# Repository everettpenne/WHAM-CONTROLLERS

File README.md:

# WHAM controllers

Firmware, hardware files and host software for the WHAM controller board (STM32G474QET6) and the two
products that run on it.

```
firmware/
  xrex/      WHAM-XREX-PFMG474    Transrex magnet-supply PFM PID controller
  hbridge/   WHAM-HBRIDGE-PFMG474 3-phase H-bridge (Limiter PWM / HVPS PFM)
hardware/    board files, pin map, hardware notes (see hardware/README.md)
host/        host-side software that talks to the boards: the per-controller service (see docs/)
docs/        design documents that span products (identity, host service, repo layout)
```

Each firmware directory is a complete, self-contained project (its own AGENTS.md, build, tests, docs) and keeps its own
history, imported from the former standalone repositories. Code that both products share is still copied byte-for-byte
and guarded by `firmware/<product>/python/check_shared.py`; see each project's `docs/saved_profiles_shared.md`.

## History

This repository replaces the standalone `WHAM-XREX-PFMG474` and `WHAM-HBRIDGE-PFMG474` repositories (imported on 2026-10-07 with their
full histories; the old repositories stop at that point and are no longer updated). All the projects are maintained here from now on:
firmware for both products, the hardware files, the host software and the design documents. `docs/device_identity_and_host_service.md`
is the plan for board identity and the host service.

## License

The software is licensed under the GNU Affero General Public License v3.0 only (`AGPL-3.0-only`): see [`LICENSE`](LICENSE).
What that covers, what keeps its own license (the ST and Arm vendor code), and what is not licensed yet (documents and
hardware designs) is spelled out in [`LICENSING.md`](LICENSING.md).

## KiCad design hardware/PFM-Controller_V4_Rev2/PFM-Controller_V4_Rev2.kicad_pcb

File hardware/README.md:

# Hardware

KiCad projects for the WHAM controller board and its predecessors, with their fabrication outputs.

| Folder | What |
|---|---|
| `PFM-Controller_V4/` | the current controller board (STM32G474QET6, pin map in `firmware/*/docs/pin_mapping_v4.csv`) |
| `PFM-Controller_V4_Rev2/` | a second revision of the V4 board (KiCad project) |
| `HVPS_Controller_V3/` | the previous board (V3) |

Not tracked on purpose (see `.gitignore`): KiCad backups, autosaves and caches, the fabrication toolkit's `production/backups/`, and
large third-party document archives (`hardware/*.zip`; GitHub refuses files over 100 MB). `PFM-Controller_V4/PFMV4_Prelim_Files-main/`
(a downloaded copy of earlier project files and documents) is left untracked until someone decides it belongs here.

The pin map still lives with each firmware project (the firmware, the SOP and the command reference point at it). Moving it here, with
product columns beside it and a changelog of board revisions, is the natural next step.

**License:** the hardware designs are not licensed yet (all rights reserved); the AGPL in the repository root covers the software only.
See `LICENSING.md`.

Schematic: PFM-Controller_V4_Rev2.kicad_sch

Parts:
C1, C2: 100u
C31, C61, C62, C63, C64, C65, C66, C67, C68, C69, C70, C71, C72, C73, C74, C75, C76, C77, C78, C79, C80, C81, C82, C83, C84, C85, C86, C87, C88, C89, C90, C91, C92, C93, C94, C95, C96, C97, C98, C99, C100, C101, C102, C103, C104, C105, C112, C116, C117, C118, C124, C125, C126, C127, C129, C130: 100n; C_0805_2012Metric_Pad1.18x1.45mm_HandSolder
C33, C36, C37, C38, C39, C40, C41, C42, C43: 100n; C_0603_1608Metric_Pad1.08x0.95mm_HandSolder
C44: 10u; C_0603_1608Metric_Pad1.08x0.95mm_HandSolder
C45, C47: 1u; C_0603_1608Metric_Pad1.08x0.95mm_HandSolder
C46: 10n; C_0603_1608Metric_Pad1.08x0.95mm_HandSolder
C48, C113, C119, C121, C123: 100n; R_0603_1608Metric_Pad0.98x0.95mm_HandSolder
C49, C50: 16pF; C_0805_2012Metric_Pad1.18x1.45mm_HandSolder
C51, C52, C53, C54, C55, C56, C58, C138, C139, C140, C141, C142, C143, C144, C145, C146: C; C_1206_3216Metric_Pad1.33x1.80mm_HandSolder; not fitted
C59: 10n; C_1206_3216Metric_Pad1.33x1.80mm_HandSolder
C60: 1u; C_1206_3216Metric_Pad1.33x1.80mm_HandSolder
C106, C107, C108, C109, C110, C111, C114, C120, C131, C132, C133, C134, C135, C136, C137, C147, C148, C149, C150, C151, C152, C153: 100n; C_1206_3216Metric_Pad1.33x1.80mm_HandSolder
D1, D2, D3, D4, D6, D7, D8, D9: BAV99S; SOT-363_SC-70-6
D5, D10, D11, D12, D13, D14, D15, D16: LED; LED_0805_2012Metric
D17, D18, D19, D20: CMKD4448; SOT-363_SC-70-6
FB1: 120R @ 100MHz; Ferrite_1206_3216Metric_Pad1.42x1.75mm_BigPads
FB2, FB3, FB4, FB5, FB6, FB7, FB8, FB9, FB10, FB11, FB12, FB13, FB14, FB15, FB16, FB17, FB18, FB19, FB20, FB21, FB22, FB23, FB24, FB25, FB26, FB27: 110R @ 30MHz; Ferrite_1206_3216Metric_Pad1.42x1.75mm_BigPads
H1, H2, H3, H4, H5, H6, H7, H8, H9, H10, H11, H12, H13, H14, H15, H16, H17, H18: MountingHole; MountingHole_2mm
IC1, IC2, IC3, IC4, IC5, IC6, IC7, IC8, IC9, IC10, IC11, IC12, IC13, IC14, IC15, IC16, IC17, IC18, IC19, IC20, IC21: IX4340NTR; SOIC-8_3.9x4.9mm_P1.27mm; Mouser Part Number 747-IX4340NTR
J1, J2, J3, J4, J5, J6, J7, J8: BNC; BNC_TEConnectivity_1478204_Vertical; not fitted
J9: Conn_01x04_Pin; Molex_KK-254_AE-6410-04A_1x04_P2.54mm_Vertical
J10, J11, J12, J20: Molex 01x03; Molex_KK-254_AE-6410-03A_1x03_P2.54mm_Vertical
J13: Conn_01x04_Pin; Molex_KK-396_5273-04A_1x04_P3.96mm_Vertical
J16: Conn_01x06_Pin; Molex_KK-254_AE-6410-06A_1x06_P2.54mm_Vertical
J21: Conn_01x30_Pin; PinHeader_2x15_P2.54mm_Vertical
J22: Conn_01x16_Pin; PinHeader_2x08_P2.54mm_Vertical
R1, R2, R3, R4, R5, R6, R9, R10, R11, R12, R13, R14, R30, R31, R41, R63, R65, R92, R209, R228: 5K; R_0805_2012Metric_Pad1.20x1.40mm_HandSolder
R7, R27, R28, R29, R32, R33, R46, R47, R71, R74, R76, R104, R106, R108, R110, R112, R114, R117, R119: 5K; R_1206_3216Metric_Pad1.30x1.75mm_HandSolder
R15, R16, R17, R18, R19, R20, R21, R22, R23, R24, R25, R26, R51, R52, R53, R54, R55, R56, R57, R58, R59, R60, R61, R62, R77, R78, R95, R96, R97, R98, R99, R100, R101, R102, R115, R123, R124, R204, R205, R207: 62; R_1206_3216Metric_Pad1.30x1.75mm_HandSolder
R34, R66, R81, R82, R83, R84, R85, R86, R87, R88, R89, R90, R91, R93, R94, R122, R133, R136, R137, R138, R139, R140, R141, R148, R149, R152, R153, R217, R219, R221, R222, R223, R224: 62; R_0805_2012Metric_Pad1.20x1.40mm_HandSolder
R35, R36, R37, R38, R39, R40: NC; R_1206_3216Metric_Pad1.30x1.75mm_HandSolder; not fitted
R42: 10K; R_1206_3216Metric_Pad1.30x1.75mm_HandSolder
R43, R44: 100K; R_1206_3216Metric_Pad1.30x1.75mm_HandSolder
R45: 20; R_0603_1608Metric_Pad0.98x0.95mm_HandSolder
R48, R210, R211: 0; R_1206_3216Metric_Pad1.30x1.75mm_HandSolder; not fitted
R49, R50, R120, R121, R127, R212: 0; R_1206_3216Metric_Pad1.30x1.75mm_HandSolder
R64, R126, R145, R147, R150, R151, R156, R157, R158, R159, R160, R161, R162, R163, R164, R165, R166, R167, R168, R169, R170, R171, R172, R173, R174, R175, R176, R177, R178, R179, R180, R181, R186, R187, R188, R189, R190, R191, R193, R194, R197, R198, R201, R202, R206, R213, R216: 0; R_0805_2012Metric_Pad1.20x1.40mm_HandSolder
R67: NC; R_0805_2012Metric_Pad1.20x1.40mm_HandSolder; not fitted
R68, R69, R70, R72, R73, R75, R79, R80: 62; R_1206_3216Metric_Pad1.30x1.75mm_HandSolder; not fitted
R103, R105, R107, R109, R111, R113, R116, R118: 2.5K; R_1206_3216Metric_Pad1.30x1.75mm_HandSolder
R125: 1K; R_0805_2012Metric_Pad1.20x1.40mm_HandSolder
R129, R130, R131, R132, R218, R220: 62; R_0805_2012Metric_Pad1.20x1.40mm_HandSolder; not fitted
R134, R135, R142, R143, R144, R146, R154, R155, R184, R185, R192, R195, R196, R199, R200, R203, R208, R214, R215: 0; R_0805_2012Metric_Pad1.20x1.40mm_HandSolder; not fitted
R182, R183: R; R_1206_3216Metric_Pad1.30x1.75mm_HandSolder
R225, R226, R227: 5K; R_0805_2012Metric_Pad1.20x1.40mm_HandSolder; not fitted
R229, R231, R232, R233, R234, R235, R236: 680; R_0805_2012Metric_Pad1.20x1.40mm_HandSolder
R230: 1.5K; R_0805_2012Metric_Pad1.20x1.40mm_HandSolder
SW1: Molex 01x03; Molex_KK-254_AE-6410-03A_1x03_P2.54mm_Vertical
U1: STM32G474QET6; LQFP-128_14x14mm_P0.4mm
U2: W25Q128JVS; SOIC-8_5.3x5.3mm_P1.27mm
U3, U34, U35, U75, U76, U77: MCP6009; TSSOP-14_4.4x5mm_P0.65mm
U4, U5, U6, U7, U8, U9, U10, U11, U12, U13, U14, U15: VersalinkTX; Versalink-Vertical
U16, U18, U20, U48, U51, U57, U72: SN74LVC2G14DBVR; SOT-23-6
U17, U19, U21, U49, U71, U73, U74: SN74LVC2G08DCUT; SOP50P310X90-8N
U22, U23, U24, U25, U26, U27, U28, U29, U30, U31, U32, U33, U36, U37, U38, U39, U40, U41, U42, U43, U44, U45, U46, U47, U50, U52, U78, U79: VersalinkRX; Versalink-Vertical
U53, U54, U80, U81, U82: 74HC14; SOIC-14_3.9x8.7mm_P1.27mm
U55, U56: SN74HC21DR1G4; SOIC-14_3.9x8.7mm_P1.27mm
U58: GPOut_01; Versalink-Vertical
U59: GPOut_02; Versalink-Vertical
U60: GPOut_03; Versalink-Vertical
U61: GPOut_04; Versalink-Vertical
U62: GPOut_05; Versalink-Vertical
U63: GPOut_06; Versalink-Vertical
U64: GPOut_07; Versalink-Vertical
U65: GPOut_08; Versalink-Vertical
U66: GPOut_09; Versalink-Vertical
U67: GPOut_10; Versalink-Vertical
U68: GPOut_11; Versalink-Vertical
U69: GPOut_12; Versalink-Vertical
U70: AMS1117CD-3.3; TO-252-3_TabPin2
U83: 74LS08
Y1: ECS-80-12-33-JGN-TR-CT-ND; Crystal_SMD_3225-4Pin_3.2x2.5mm_HandSoldering; JLC Part # C9900261642

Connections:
+3V3: C31.1, C33.1, C36.1, C37.1, C38.1, C39.1, C40.1, C41.1, C42.1, C43.1, C44.1, C47.1, C59.1, C60.1, C106.1, C107.1, C108.1, C120.1, C151.1, D5.2 (A), D6.2 (K2), D6.5 (K4), D7.2 (K2), D7.5 (K4), D8.2 (K2), D8.5 (K4), D9.2 (K2), D9.5 (K4), FB1.2, J16.5, J21.27, R42.1, R43.1, R44.1, R120.2, R121.2, R127.2, R182.1, R209.2, R226.2, R228.2, SW1.1 (C), U1.6 (VBAT), U1.13 (VDD), U1.31 (VDD), U1.47 (VDD), U1.64 (VDD), U1.79 (VDD), U1.95 (VDD), U1.111 (VDD), U1.128 (VDD), U2.8 (VCC), U53.14 (VCC), U54.14 (VCC), U70.2 (VO), U80.14 (VCC), U81.14 (VCC), U82.14 (VCC)
+3V3in: J9.1, J9.2, R120.1, R121.1, R127.1
+5Vin: C1.1, C2.1, C61.1, C62.1, C63.1, C64.1, C65.1, C66.1, C67.1, C68.1, C69.1, C70.1, C71.1, C72.1, C73.1, C74.1, C75.1, C76.1, C77.1, C78.1, C79.1, C80.1, C81.1, C82.1, C83.1, C84.1, C85.1, C86.1, C87.1, C88.1, C89.1, C90.1, C91.1, C92.1, C93.1, C94.1, C95.1, C96.1, C97.1, C98.1, C99.1, C109.1, C110.1, C111.1, C112.1, C114.1, C116.1, C117.1, C118.1, C124.1, C125.1, C126.1, C127.1, C129.1, C130.1, C131.1, C132.1, C133.1, C134.1, C135.1, C136.1, C137.1, C147.1, C148.1, C149.1, C150.1, C152.1, C153.1, D1.2 (K2), D1.5 (K4), D2.2 (K2), D2.5 (K4), D3.2 (K2), D3.5 (K4), D4.2 (K2), D4.5 (K4), D10.2 (A), IC1.6 (VCC), IC2.6 (VCC), IC3.6 (VCC), IC4.6 (VCC), IC5.6 (VCC), IC6.6 (VCC), IC7.6 (VCC), IC8.6 (VCC), IC9.6 (VCC), IC10.1 (ENA), IC10.6 (VCC), IC10.8 (ENB), IC11.1 (ENA), IC11.6 (VCC), IC11.8 (ENB), IC12.1 (ENA), IC12.6 (VCC), IC12.8 (ENB), IC13.1 (ENA), IC13.6 (VCC), IC13.8 (ENB), IC14.6 (VCC), IC15.6 (VCC), IC16.6 (VCC), IC17.1 (ENA), IC17.6 (VCC), IC17.8 (ENB), IC18.1 (ENA), IC18.6 (VCC), IC18.8 (ENB), IC19.1 (ENA), IC19.6 (VCC), IC19.8 (ENB), IC20.1 (ENA), IC20.6 (VCC), IC20.8 (ENB), IC21.1 (ENA), IC21.6 (VCC), IC21.8 (ENB), J13.3, J13.4, J21.29, R49.1, R50.1, R67.2, R183.1, R211.1, R213.1, U3.4 (V+), U16.5 (V_{CC}), U17.8 (VCC), U18.5 (V_{CC}), U19.8 (VCC), U20.5 (V_{CC}), U21.8 (VCC), U22.3 (VCC), U23.3 (VCC), U24.3 (VCC), U25.3 (VCC), U26.3 (VCC), U27.3 (VCC), U28.3 (VCC), U29.3 (VCC), U30.3 (VCC), U31.3 (VCC), U32.3 (VCC), U33.3 (VCC), U34.4 (V+), U35.4 (V+), U36.3 (VCC), U37.3 (VCC), U38.3 (VCC), U39.3 (VCC), U40.3 (VCC), U41.3 (VCC), U42.3 (VCC), U43.3 (VCC), U44.3 (VCC), U45.3 (VCC), U46.3 (VCC), U47.3 (VCC), U48.5 (V_{CC}), U49.8 (VCC), U50.3 (VCC), U51.5 (V_{CC}), U52.3 (VCC), U55.14 (VCC), U56.14 (VCC), U57.5 (V_{CC}), U70.3 (VI), U71.8 (VCC), U72.5 (V_{CC}), U73.8 (VCC), U74.8 (VCC), U75.4 (V+), U76.4 (V+), U77.4 (V+), U78.3 (VCC), U79.3 (VCC)
AnalogIn_01: R95.1, R103.1, R104.2, R115.1, U1.27 (PA0)
AnalogIn_01_Out: FB2.2, J22.11
AnalogIn_02: R97.1, R105.1, R106.2, R123.1, U1.28 (PA1)
AnalogIn_02_Out: FB3.2, J22.9
AnalogIn_03: R77.1, R99.1, R107.1, R108.2, U1.22 (PC0)
AnalogIn_03_Out: FB4.2, J22.15
AnalogIn_04: R78.1, R101.1, R109.1, R110.2, U1.39 (PB0)
AnalogIn_04_Out: FB5.2, J22.3
AnalogIn_05: R96.1, R111.1, R112.2, R124.1, U1.23 (PC1)
AnalogIn_05_Out: FB18.2, J22.13
AnalogIn_06: R98.1, R113.1, R114.2, R204.1, U1.40 (PB1)
AnalogIn_06_Out: FB19.2, J22.1
AnalogOut_01: R100.1, R118.1, R119.2, R205.1, U1.33 (PA4)
AnalogOut_01_Out: FB20.2, J22.7
AnalogOut_02: R102.1, R116.1, R117.2, R207.1, U1.34 (PA5)
AnalogOut_02_Out: FB21.2, J22.5
BOOT0: C119.1, R63.1, R65.2, U1.123 (PB8)
FDCAN2_RX: R220.2, U1.120 (PB5)
FDCAN2_TX: R218.1, U1.121 (PB6)
Fiber_Enable: R66.2, R67.1, U1.52 (PF15), U74.5 (2A)
Fiber_Trigger: C121.2, R94.2, R125.1, U1.101 (PC11)
GND: C1.2, C2.2, C31.2, C33.2, C36.2, C37.2, C38.2, C39.2, C40.2, C41.2, C42.2, C43.2, C44.2, C45.2, C46.2, C47.2, C48.2, C49.2, C50.2, C51.2, C52.2, C53.2, C54.2, C55.2, C56.2, C58.2, C59.2, C60.2, C61.2, C62.2, C63.2, C64.2, C65.2, C66.2, C67.2, C68.2, C69.2, C70.2, C71.2, C72.2, C73.2, C74.2, C75.2, C76.2, C77.2, C78.2, C79.2, C80.2, C81.2, C82.2, C83.2, C84.2, C85.2, C86.2, C87.2, C88.2, C89.2, C90.2, C91.2, C92.2, C93.2, C94.2, C95.2, C96.2, C97.2, C98.2, C99.2, C100.2, C101.2, C102.2, C103.2, C104.2, C105.2, C106.2, C107.2, C108.2, C109.2, C110.2, C111.2, C112.2, C113.1, C114.2, C116.2, C117.2, C118.2, C119.2, C120.2, C121.1, C123.1, C124.2, C125.2, C126.2, C127.2, C129.2, C130.2, C131.2, C132.2, C133.2, C134.2, C135.2, C136.2, C137.2, C138.2, C139.2, C140.2, C141.2, C142.2, C143.2, C144.2, C145.2, C146.2, C147.2, C148.2, C149.2, C150.2, C151.2, C152.2, C153.2, D1.1 (A1), D1.4 (A3), D2.1 (A1), D2.4 (A3), D3.1 (A1), D3.4 (A3), D4.1 (A1), D4.4 (A3), D6.1 (A1), D6.4 (A3), D7.1 (A1), D7.4 (A3), D8.1 (A1), D8.4 (A3), D9.1 (A1), D9.4 (A3), IC1.3 (GND), IC2.3 (GND), IC3.3 (GND), IC4.3 (GND), IC5.3 (GND), IC6.3 (GND), IC7.3 (GND), IC8.3 (GND), IC9.3 (GND), IC10.3 (GND), IC11.3 (GND), IC12.3 (GND), IC13.3 (GND), IC14.3 (GND), IC15.3 (GND), IC16.3 (GND), IC17.3 (GND), IC18.3 (GND), IC19.3 (GND), IC20.3 (GND), IC21.3 (GND), J1.2 (Ext), J2.2 (Ext), J3.2 (Ext), J4.2 (Ext), J5.2 (Ext), J6.2 (Ext), J7.2 (Ext), J8.2 (Ext), J9.3, J9.4, J10.3, J11.3, J12.3, J13.1, J13.2, J16.6, J20.2, J21.2, J21.4, J21.6, J21.8, J21.10, J21.12, J21.14, J21.16, J21.18, J21.20, J21.22, J21.24, J21.25, J21.26, J21.28, J21.30, J22.2, J22.4, J22.6, J22.8, J22.10, J22.12, J22.14, J22.16, R1.2, R2.2, R3.2, R4.2, R5.2, R6.2, R7.2, R9.2, R10.2, R11.2, R12.2, R13.2, R14.2, R30.2, R31.2, R32.2, R33.2, R51.1, R52.1, R53.1, R54.1, R55.1, R56.1, R57.1, R58.1, R59.1, R60.1, R61.1, R62.1, R68.1, R69.1, R70.1, R72.1, R73.1, R75.1, R79.1, R80.1, R92.1, R104.1, R106.1, R108.1, R110.1, R112.1, R114.1, R117.1, R119.1, R122.1, R125.2, R225.1, R227.1, R229.2, R230.2, R231.2, R232.2, R233.2, R234.2, R235.2, R236.2, SW1.3 (A), U1.12 (VSS), U1.30 (VSS), U1.42 (VSSA), U1.46 (VSS), U1.63 (VSS), U1.78 (VSS), U1.94 (VSS), U1.110 (VSS), U1.127 (VSS), U2.4 (GND), U3.11 (V-), U4.2 (Cathode), U5.2 (Cathode), U6.2 (Cathode), U7.2 (Cathode), U8.2 (Cathode), U9.2 (Cathode), U10.2 (Cathode), U11.2 (Cathode), U12.2 (Cathode), U13.2 (Cathode), U14.2 (Cathode), U15.2 (Cathode), U16.2 (GND), U17.4 (GND), U18.2 (GND), U19.4 (GND), U20.2 (GND), U21.4 (GND), U22.2 (GND), U23.2 (GND), U24.2 (GND), U25.2 (GND), U26.2 (GND), U27.2 (GND), U28.2 (GND), U29.2 (GND), U30.2 (GND), U31.2 (GND), U32.2 (GND), U33.2 (GND), U34.11 (V-), U35.11 (V-), U36.2 (GND), U37.2 (GND), U38.2 (GND), U39.2 (GND), U40.2 (GND), U41.2 (GND), U42.2 (GND), U43.2 (GND), U44.2 (GND), U45.2 (GND), U46.2 (GND), U47.2 (GND), U48.2 (GND), U49.4 (GND), U50.2 (GND), U51.2 (GND), U52.2 (GND), U53.7 (GND), U54.7 (GND), U55.7 (GND), U56.7 (GND), U57.2 (GND), U57.3 (2A), U70.1 (GND), U71.4 (GND), U72.2 (GND), U73.4 (GND), U74.4 (GND), U75.11 (V-), U76.11 (V-), U77.11 (V-), U78.2 (GND), U79.2 (GND), U80.7 (GND), U81.7 (GND), U82.7 (GND), Y1.2, Y1.4
GPInput_03: U1.11 (PF4), U80.6
GPInput_04: U1.14 (PF5), U80.12
GPInput_07: U1.16 (PF8), U81.12
GPInput_08: U1.17 (PF9), U81.2
GPInput_11: U1.49 (PF12), U81.6
GPInput_12: R220.1, U1.50 (PF13), U81.4
GPOut_01: IC4.2 (INA), R131.2, U1.82 (PG0)
GPOut_02: IC4.4 (INB), R132.2, U1.83 (PG1)
GPOut_03: IC5.2 (INA), U1.84 (PG2)
GPOut_04: IC5.4 (INB), U1.85 (PG3)
GPOut_05: IC6.2 (INA), U1.86 (PG4)
GPOut_06: IC6.4 (INB), U1.103 (PG5)
GPOut_07: IC7.2 (INA), U1.104 (PG6)
GPOut_08: IC7.4 (INB), U1.105 (PG7)
GPOut_09: IC8.2 (INA), U1.106 (PG8)
GPOut_10: IC8.4 (INB), U1.107 (PG9)
GPOut_11: IC9.2 (INA), U1.108 (PD0)
GPOut_12: IC9.4 (INB), R218.2, U1.109 (PD1)
GPOut_Enable: C100.1, C101.1, C102.1, C103.1, C104.1, C105.1, IC4.1 (ENA), IC4.8 (ENB), IC5.1 (ENA), IC5.8 (ENB), IC6.1 (ENA), IC6.8 (ENB), IC7.1 (ENA), IC7.8 (ENB), IC8.1 (ENA), IC8.8 (ENB), IC9.1 (ENA), IC9.8 (ENB), R48.1, R49.2
GPOut_Enable_Pin: R32.1, R48.2, U1.7 (PC13)
GateDriverStatus_01: D17.2 (A), U1.125 (PE0), U53.2, U56.12
GateDriverStatus_02: D17.3 (A), U1.126 (PE1), U53.4, U56.10
GateDriverStatus_03: D17.1 (A), U1.1 (PE2), U53.6, U56.13
GateDriverStatus_04: D18.1 (A), U1.2 (PE3), U53.12, U56.9
GateDriverStatus_05: D18.2 (A), U1.3 (PE4), U53.8, U56.1
GateDriverStatus_06: D18.3 (A), U1.4 (PE5), U53.10, U56.2
GateDriverStatus_07: D19.1 (A), U1.5 (PE6), U54.2, U56.4
GateDriverStatus_08: D20.3 (A), U1.53 (PE7), U54.4, U55.1
GateDriverStatus_09: D19.2 (A), U1.54 (PE8), U54.12, U56.5
GateDriverStatus_10: D19.3 (A), U1.55 (PE9), U54.10, U55.5
GateDriverStatus_11: D20.1 (A), U1.56 (PE10), U54.8, U55.4
GateDriverStatus_12: D20.2 (A), U1.57 (PE11), U54.6, U55.2
HR_FAULT_INPUT_PIN: R31.1, R41.2, R215.2, R216.1, U74.6 (2B)
HSE_IN: C50.1, U1.19 (PF0), Y1.3
HSE_OUT: R64.1, U1.20 (PF1)
NRST: C48.1, J16.4, R126.2, R228.1, U1.21 (PG10)
unnamed: C49.1, R64.2, Y1.1
unnamed: C139.1, R103.2, R144.2, R186.2
unnamed: C140.1, R105.2, R143.2, R189.2
unnamed: C141.1, R116.2, R147.2, R154.2
unnamed: C142.1, R118.2, R151.2, R184.2
unnamed: C143.1, R107.2, R146.2, R191.2
unnamed: C144.1, R109.2, R194.2, R195.2
unnamed: C145.1, R113.2, R202.2, R203.2
unnamed: C146.1, R111.2, R198.2, R199.2
unnamed: C53.1, D1.6 (K3A4), R71.2, R135.2, R188.1
unnamed: C51.1, D1.3 (K1A2), R27.2, R134.2, R187.1
unnamed: C52.1, D2.6 (K3A4), R28.2, R192.2, R193.1
unnamed: C54.1, D2.3 (K1A2), R29.2, R142.2, R190.1
unnamed: C56.1, D3.6 (K3A4), R76.2, R200.2, R201.1
unnamed: C55.1, D3.3 (K1A2), R74.2, R196.2, R197.1
unnamed: C58.1, D4.6 (K3A4), R46.2, R145.2, R155.1
unnamed: C138.1, D4.3 (K1A2), R47.2, R150.2, R185.1
unnamed: D5.1 (K), R229.1
unnamed: D6.6 (K3A4), R78.2
unnamed: D6.3 (K1A2), R77.2
unnamed: D7.6 (K3A4), R98.2
unnamed: D7.3 (K1A2), R96.2
unnamed: D8.6 (K3A4), R102.2
unnamed: D8.3 (K1A2), R100.2
unnamed: D9.6 (K3A4), R123.2
unnamed: D9.3 (K1A2), R115.2
unnamed: D10.1 (K), R230.1
unnamed: D11.1 (K), R231.1
unnamed: D12.1 (K), R232.1
unnamed: D13.1 (K), R233.1
unnamed: D14.1 (K), R234.1
unnamed: D15.1 (K), R235.1
unnamed: D16.1 (K), R236.1
unnamed: D17.6 (K), R34.1
unnamed: D17.5 (K), R82.1
unnamed: D17.4 (K), R81.1
unnamed: D18.6 (K), R83.1
unnamed: D18.5 (K), R91.1
unnamed: D18.4 (K), R90.1
unnamed: D19.6 (K), R89.1
unnamed: D19.5 (K), R87.1
unnamed: D19.4 (K), R86.1
unnamed: D20.6 (K), R85.1
unnamed: D20.5 (K), R84.1
unnamed: D20.4 (K), R88.1
unnamed: IC1.2 (INA), U17.7 (1Y)
unnamed: IC1.4 (INB), U17.3 (2Y)
unnamed: IC2.2 (INA), U19.7 (1Y)
unnamed: IC2.4 (INB), U19.3 (2Y)
unnamed: IC3.2 (INA), U21.7 (1Y)
unnamed: IC3.4 (INB), U21.3 (2Y)
unnamed: IC4.7 (OUTA), U58.1 (Anode)
unnamed: IC4.5 (OUTB), U59.1 (Anode)
unnamed: IC5.7 (OUTA), U60.1 (Anode)
unnamed: IC5.5 (OUTB), U61.1 (Anode)
unnamed: IC6.7 (OUTA), U62.1 (Anode)
unnamed: IC6.5 (OUTB), U63.1 (Anode)
unnamed: IC7.7 (OUTA), U64.1 (Anode)
unnamed: IC7.5 (OUTB), U65.1 (Anode)
unnamed: IC8.7 (OUTA), U66.1 (Anode)
unnamed: IC8.5 (OUTB), U67.1 (Anode)
unnamed: IC9.7 (OUTA), U68.1 (Anode)
unnamed: IC9.5 (OUTB), U69.1 (Anode)
unnamed: IC10.2 (INA), R148.2
unnamed: IC10.4 (INB), R149.2
unnamed: FB6.1, IC10.7 (OUTA)
unnamed: FB7.1, IC10.5 (OUTB)
unnamed: IC11.2 (INA), R136.2
unnamed: IC11.4 (INB), R137.2
unnamed: FB8.1, IC11.7 (OUTA)
unnamed: FB9.1, IC11.5 (OUTB)
unnamed: IC12.2 (INA), R93.2
unnamed: IC12.4 (INB), R133.2
unnamed: FB10.1, IC12.7 (OUTA)
unnamed: FB11.1, IC12.5 (OUTB)
unnamed: IC13.2 (INA), R152.2
unnamed: IC13.4 (INB), R153.2
unnamed: FB14.1, IC13.7 (OUTA)
unnamed: FB15.1, IC13.5 (OUTB)
unnamed: IC14.2 (INA), U73.7 (1Y)
unnamed: IC14.4 (INB), U73.3 (2Y)
unnamed: IC15.2 (INA), U71.7 (1Y)
unnamed: IC15.4 (INB), U71.3 (2Y)
unnamed: IC16.2 (INA), U49.7 (1Y)
unnamed: IC16.4 (INB), U49.3 (2Y)
unnamed: IC17.2 (INA), R140.2
unnamed: IC17.4 (INB), R141.2
unnamed: FB13.1, IC17.7 (OUTA)
unnamed: FB16.1, IC17.5 (OUTB)
unnamed: IC18.2 (INA), R138.2
unnamed: IC18.4 (INB), R139.2
unnamed: FB12.1, IC18.7 (OUTA)
unnamed: FB17.1, IC18.5 (OUTB)
unnamed: IC19.2 (INA), R217.2
unnamed: FB22.2, IC19.4 (INB)
unnamed: FB23.1, IC19.7 (OUTA)
unnamed: IC19.5 (OUTB), R219.1
unnamed: IC20.2 (INA), R221.2
unnamed: FB24.2, IC20.4 (INB)
unnamed: FB25.1, IC20.7 (OUTA)
unnamed: IC20.5 (OUTB), R222.1
unnamed: IC21.2 (INA), R223.2
unnamed: FB26.2, IC21.4 (INB)
unnamed: FB27.1, IC21.7 (OUTA)
unnamed: IC21.5 (OUTB), R224.1
unnamed: J1.1 (In), R46.1, R79.2
unnamed: J2.1 (In), R47.1, R80.2
unnamed: J3.1 (In), R70.2, R71.1
unnamed: J4.1 (In), R27.1, R68.2
unnamed: J5.1 (In), R28.1, R69.2
unnamed: J6.1 (In), R29.1, R72.2
unnamed: J7.1 (In), R75.2, R76.1
unnamed: J8.1 (In), R73.2, R74.1
unnamed: J20.1, R182.2
unnamed: J20.3, R183.2
unnamed: R65.1, U82.2
unnamed: R66.1, U82.6
unnamed: R94.1, U82.4
unnamed: R122.2, U82.13
unnamed: R126.1, R226.1, R227.2, U82.10
unnamed: R63.2, SW1.2 (B)
unnamed: R45.1, U1.62 (PB10)
unnamed: R41.1, U1.100 (PC10)
unnamed: C113.2, U1.43 (VREF+)
unnamed: C123.2, U1.44 (VREF_+)
unnamed: R99.2, U3.3 (+)
unnamed: FB4.1, U3.1, U3.2 (-)
unnamed: R124.2, U3.5 (+)
unnamed: FB18.1, U3.6 (-), U3.7
unnamed: R95.2, U3.10 (+)
unnamed: FB2.1, U3.8, U3.9 (-)
unnamed: R97.2, U3.12 (+)
unnamed: FB3.1, U3.13 (-), U3.14
unnamed: R15.2, U4.1 (Anode)
unnamed: R16.2, R36.2, U5.1 (Anode)
unnamed: R17.2, U6.1 (Anode)
unnamed: R18.2, R35.2, U7.1 (Anode)
unnamed: R19.2, U8.1 (Anode)
unnamed: R20.2, R37.2, U9.1 (Anode)
unnamed: R21.2, U10.1 (Anode)
unnamed: R22.2, R38.2, U11.1 (Anode)
unnamed: R23.2, U12.1 (Anode)
unnamed: R24.2, R39.2, U13.1 (Anode)
unnamed: R25.2, U14.1 (Anode)
unnamed: R26.2, R40.2, U15.1 (Anode)
unnamed: U16.6 (1Y), U17.2 (1B)
unnamed: U16.4 (2Y), U17.5 (2A)
unnamed: U18.6 (1Y), U19.2 (1B)
unnamed: U18.4 (2Y), U19.5 (2A)
unnamed: U20.6 (1Y), U21.2 (1B)
unnamed: U20.4 (2Y), U21.5 (2A)
unnamed: R168.1, U22.4 (R_L)
unnamed: R168.2, U22.1 (V_O), U53.1
unnamed: R169.1, U23.4 (R_L)
unnamed: R169.2, U23.1 (V_O), U53.3
unnamed: R170.1, U24.4 (R_L)
unnamed: R170.2, U24.1 (V_O), U53.5
unnamed: R171.1, U25.4 (R_L)
unnamed: R171.2, U25.1 (V_O), U53.13
unnamed: R172.1, U26.4 (R_L)
unnamed: R172.2, U26.1 (V_O), U53.9
unnamed: R173.1, U27.4 (R_L)
unnamed: R173.2, U27.1 (V_O), U53.11
unnamed: R174.1, U28.4 (R_L)
unnamed: R174.2, U28.1 (V_O), U54.1
unnamed: R175.1, U29.4 (R_L)
unnamed: R175.2, U29.1 (V_O), U54.3
unnamed: R176.1, U30.4 (R_L)
unnamed: R176.2, U30.1 (V_O), U54.13
unnamed: R177.1, U31.4 (R_L)
unnamed: R177.2, U31.1 (V_O), U54.11
unnamed: R178.1, U32.4 (R_L)
unnamed: R178.2, U32.1 (V_O), U54.9
unnamed: R179.1, U33.4 (R_L)
unnamed: R179.2, U33.1 (V_O), U54.5
unnamed: R188.2, U34.3 (+)
unnamed: R189.1, U34.1, U34.2 (-)
unnamed: R187.2, U34.5 (+)
unnamed: R186.1, U34.6 (-), U34.7
unnamed: R144.1, U34.10 (+)
unnamed: R134.1, U34.8, U34.9 (-)
unnamed: R143.1, U34.12 (+)
unnamed: R135.1, U34.13 (-), U34.14
unnamed: R155.2, U35.3 (+)
unnamed: R154.1, U35.1, U35.2 (-)
unnamed: R185.2, U35.5 (+)
unnamed: R184.1, U35.6 (-), U35.7
unnamed: R151.1, U35.10 (+)
unnamed: R150.1, U35.8, U35.9 (-)
unnamed: R147.1, U35.12 (+)
unnamed: R145.1, U35.13 (-), U35.14
unnamed: R156.1, U36.4 (R_L)
unnamed: R156.2, U36.1 (V_O), U80.1
unnamed: R157.1, U37.4 (R_L)
unnamed: R157.2, U37.1 (V_O), U80.3
unnamed: R158.1, U38.4 (R_L)
unnamed: R158.2, U38.1 (V_O), U80.5
unnamed: R159.1, U39.4 (R_L)
unnamed: R159.2, U39.1 (V_O), U80.13
unnamed: R160.1, U40.4 (R_L)
unnamed: R160.2, U40.1 (V_O), U80.9
unnamed: R161.1, U41.4 (R_L)
unnamed: R161.2, U41.1 (V_O), U80.11
unnamed: R162.1, U42.4 (R_L)
unnamed: R162.2, U42.1 (V_O), U81.13
unnamed: R163.1, U43.4 (R_L)
unnamed: R163.2, U43.1 (V_O), U81.1
unnamed: R164.1, U44.4 (R_L)
unnamed: R164.2, U44.1 (V_O), U81.11
unnamed: R165.1, U45.4 (R_L)
unnamed: R165.2, U45.1 (V_O), U81.9
unnamed: R166.1, U46.4 (R_L)
unnamed: R166.2, U46.1 (V_O), U81.5
unnamed: R167.1, U47.4 (R_L)
unnamed: R167.2, U47.1 (V_O), U81.3
unnamed: U48.6 (1Y), U49.2 (1B)
unnamed: U48.4 (2Y), U49.5 (2A)
unnamed: R206.1, U50.4 (R_L)
unnamed: R206.2, U50.1 (V_O), U82.1
unnamed: U51.6 (1Y), U71.2 (1B)
unnamed: U51.4 (2Y), U71.5 (2A)
unnamed: R208.1, U52.4 (R_L)
unnamed: R208.2, R209.1, R225.2, U52.1 (V_O), U82.9
unnamed: U55.9, U56.8
unnamed: U55.10, U55.12, U56.6
unnamed: U55.6, U55.13
unnamed: R34.2, R81.2, R82.2, R83.2, R84.2, R85.2, R86.2, R87.2, R88.2, R89.2, R90.2, R91.2, R92.2, U57.1 (1A)
unnamed: R51.2, U58.2 (Cathode)
unnamed: R52.2, U59.2 (Cathode)
unnamed: R53.2, U60.2 (Cathode)
unnamed: R54.2, U61.2 (Cathode)
unnamed: R55.2, U62.2 (Cathode)
unnamed: R56.2, U63.2 (Cathode)
unnamed: R57.2, U64.2 (Cathode)
unnamed: R58.2, U65.2 (Cathode)
unnamed: R59.2, U66.2 (Cathode)
unnamed: R60.2, U67.2 (Cathode)
unnamed: R61.2, U68.2 (Cathode)
unnamed: R62.2, U69.2 (Cathode)
unnamed: U72.6 (1Y), U73.2 (1B)
unnamed: U72.4 (2Y), U73.5 (2A)
unnamed: U74.1 (1A), U74.3 (2Y)
unnamed: R30.1, R214.2, U74.7 (1Y)
unnamed: R193.2, U75.3 (+)
unnamed: R194.1, U75.1, U75.2 (-)
unnamed: R190.2, U75.5 (+)
unnamed: R191.1, U75.6 (-), U75.7
unnamed: R146.1, U75.10 (+)
unnamed: R142.1, U75.8, U75.9 (-)
unnamed: R195.1, U75.12 (+)
unnamed: R192.1, U75.13 (-), U75.14
unnamed: R201.2, U76.3 (+)
unnamed: R202.1, U76.1, U76.2 (-)
unnamed: R197.2, U76.5 (+)
unnamed: R198.1, U76.6 (-), U76.7
unnamed: R199.1, U76.10 (+)
unnamed: R196.1, U76.8, U76.9 (-)
unnamed: R203.1, U76.12 (+)
unnamed: R200.1, U76.13 (-), U76.14
unnamed: R205.2, U77.3 (+)
unnamed: FB20.1, U77.1, U77.2 (-)
unnamed: R207.2, U77.5 (+)
unnamed: FB21.1, U77.6 (-), U77.7
unnamed: R101.2, U77.10 (+)
unnamed: FB5.1, U77.8, U77.9 (-)
unnamed: R204.2, U77.12 (+)
unnamed: FB19.1, U77.13 (-), U77.14
unnamed: R180.1, U78.4 (R_L)
unnamed: R180.2, U78.1 (V_O), U82.5
unnamed: R181.1, U79.4 (R_L)
unnamed: R181.2, U79.1 (V_O), U82.3
unnamed: U82.8, U82.11
Normally_High_GD_Enable: R215.1, U55.8
Normally_Low_GD_Enable: R216.2, U57.6 (1Y)
PFM_Input_01/GPInput_01: R129.1, U1.99 (PA15), U80.2
PFM_Input_02/GPInput_05: U1.114 (PD4), U80.8
PFM_Input_03/GPInput_09: U1.41 (PB2), U81.10
PFM_Input_04/GPInput_02: R130.1, U1.102 (PC12), U80.4
PFM_Input_05/GPInput_06: U1.119 (PB4), U80.10
PFM_Input_06/GPInput_10: U1.74 (PD12), U81.8
PHASE_U: IC2.7 (OUTA), R19.1, R20.1
PHASE_UN: IC2.5 (OUTB), R21.1, R22.1
PHASE_UN_Out: FB7.2, J21.3
PHASE_UN_PIN: R3.1, R133.1, U1.90 (PA9), U18.1 (1A), U19.6 (2B)
PHASE_U_Out: FB6.2, J21.1
PHASE_U_PIN: R4.1, R93.1, U1.89 (PA8), U18.3 (2A), U19.1 (1A)
PHASE_V: IC3.7 (OUTA), R23.1, R24.1
PHASE_VN: IC3.5 (OUTB), R25.1, R26.1
PHASE_VN_Out: FB9.2, J21.7
PHASE_VN_PIN: R1.1, R137.1, U1.92 (PA11), U20.1 (1A), U21.6 (2B)
PHASE_V_Out: FB8.2, J21.5
PHASE_V_PIN: R2.1, R136.1, U1.91 (PA10), U20.3 (2A), U21.1 (1A)
PHASE_W: IC1.7 (OUTA), R15.1, R16.1
PHASE_WN: IC1.5 (OUTB), R17.1, R18.1
PHASE_WN_Out: FB11.2, J21.11
PHASE_WN_PIN: R5.1, R139.1, U1.67 (PB13), U16.1 (1A), U17.6 (2B)
PHASE_W_Out: FB10.2, J21.9
PHASE_W_PIN: R6.1, R138.1, U1.66 (PB12), U16.3 (2A), U17.1 (1A)
PHASE_X: IC15.7 (OUTA), R37.1
PHASE_XN: IC15.5 (OUTB), R38.1
PHASE_XN_Out: FB15.2, J21.15
PHASE_XN_PIN: R14.1, R141.1, U1.69 (PB15), U51.1 (1A), U71.6 (2B)
PHASE_X_Out: FB14.2, J21.13
PHASE_X_PIN: R13.1, R140.1, U1.68 (PB14), U51.3 (2A), U71.1 (1A)
PHASE_Y: IC16.7 (OUTA), R39.1
PHASE_YN: IC16.5 (OUTB), R40.1
PHASE_YN_Out: FB16.2, J21.19
PHASE_YN_PIN: R9.1, R149.1, U1.88 (PC9), U48.1 (1A), U49.6 (2B)
PHASE_Y_Out: FB13.2, J21.17
PHASE_Y_PIN: R10.1, R148.1, U1.87 (PC8), U48.3 (2A), U49.1 (1A)
PHASE_Z: IC14.7 (OUTA), R36.1
PHASE_ZN: IC14.5 (OUTB), R35.1
PHASE_ZN_Out: FB17.2, J21.23
PHASE_ZN_PIN: R11.1, R153.1, U1.81 (PC7), U72.1 (1A), U73.6 (2B)
PHASE_Z_Out: FB12.2, J21.21
PHASE_Z_PIN: R12.1, R152.1, U1.80 (PC6), U72.3 (2A), U73.1 (1A)
PWM_Alt_Enable: IC14.1 (ENA), IC14.8 (ENB), IC15.1 (ENA), IC15.8 (ENB), IC16.1 (ENA), IC16.8 (ENB), R211.2, R212.1
PWM_Alt_Enable_Pin: R7.1, R212.2, U1.9 (PC15)
PWM_Enable: IC1.1 (ENA), IC1.8 (ENB), IC2.1 (ENA), IC2.8 (ENB), IC3.1 (ENA), IC3.8 (ENB), R213.2, R214.1
QUADSPI_BK1_IO0: U1.58 (PE12), U2.5 (DI/IO_{0})
QUADSPI_BK1_IO1: U1.59 (PE13), U2.2 (DO/IO_{1})
QUADSPI_BK1_IO2: R43.2, U1.60 (PE14), U2.3 (~WP/IO_{2})
QUADSPI_BK1_IO3: R44.2, U1.61 (PE15), U2.7 (~HOLD/~RESET/IO_{3})
QUADSPI_BK1_NCS: R42.2, U1.65 (PB11), U2.1 (~CS)
QUADSPI_CLK: R45.2, U2.6 (CLK)
STATE_ARMED_LED: D14.2 (A), U1.26 (PF2)
STATE_FAULT_LED: D16.2 (A), U1.24 (PC2)
STATE_FIRING_LED: D15.2 (A), U1.25 (PC3)
STATE_IDLE_LED: D13.2 (A), U1.51 (PF14)
STM_Enable: R50.2, R210.1
STM_Enable_Pin: R33.1, R210.2, U1.8 (PC14), U74.2 (1B)
SWCLK: J16.2, U1.98 (PA14)
SWDIO: J16.1, U1.96 (PA13)
SWO: J16.3, U1.118 (PB3)
UART_RX_LED: D12.2 (A), U1.113 (PD3)
UART_TX_LED: D11.2 (A), U1.112 (PD2)
USART1_RX: R129.2, R219.2, U1.38 (PC5)
USART1_RX_In: FB22.1, J10.2
USART1_TX: R131.1, R217.1, U1.37 (PC4)
USART1_TX_Out: FB23.2, J10.1
USART2_RX: R222.2, U1.32 (PA3)
USART2_RX_In: FB24.1, J11.2
USART2_TX: R221.1, U1.29 (PA2)
USART2_TX_Out: FB25.2, J11.1
USART3_RX: R130.2, R224.2, U1.71 (PD9)
USART3_RX_In: FB26.1, J12.2
USART3_TX: R132.1, R223.1, U1.70 (PD8)
USART3_TX_Out: FB27.2, J12.1
VDDA: C45.1, C46.1, FB1.1, U1.45 (VDDA)

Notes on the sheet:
ADC3_IN2
USART3_RX
ADC345_IN14
Remote STM32 reset
Pin Header (Serial Comm)
ADC345_IN11
PWM_Enable: The PWM_Enable net controls when the PWM Fiber Gate Driver ICs drive the PWM fiber transmitters. If at any time PWM_Enable is pulled LOW (0V), all IX4340NTR outputs will immediately be driven to 0V and the versatile link transmitters stop transmitting a fiber optic signal. All 12 FET bo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
HRTIM_CHA2
Analog_06
HRTIM_CHB1
ADC2_IN11
ADC2_IN12
USART3_TX
ADC2_IN3
USART2_TX
AnalogIn_04
HRTIM_CHA1
ADC345_IN15
Analog_05
ADC3_IN5
Analog_02
ADC4_IN13/ADC5_IN13
ADC1_IN4
Gate Driver Status Fibers RX
ADC345_IN16
ABCD
PWM Fiber Enable
ADC12_IN7
ADC4_IN4/ADC1_IN5
Normally HIGH GDS, AND Block
USART1_TX
Normally LOW GDS, NOR Block
HRTIM1_CHC1
ADC4_IN1
Input/Ouput Pins
ADC4_IN2
Gate Driver Fault & Enable Handling
AnalogOut_02
EFGH
HRTIM1_CHB2

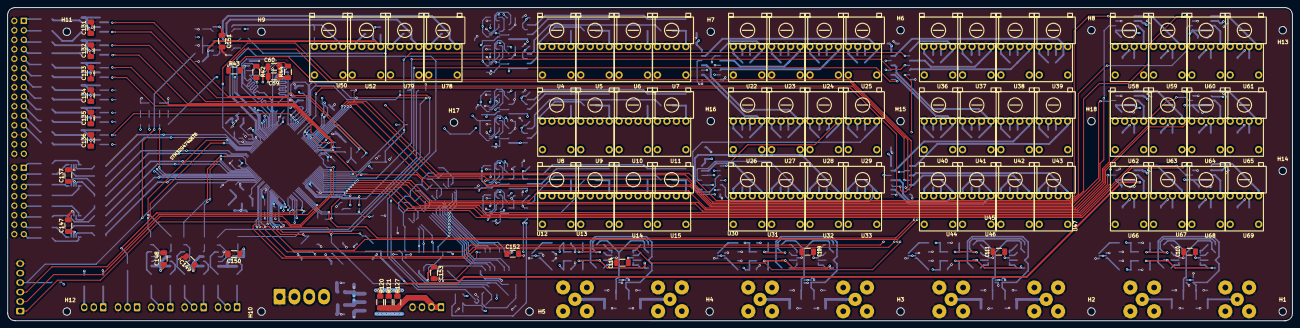
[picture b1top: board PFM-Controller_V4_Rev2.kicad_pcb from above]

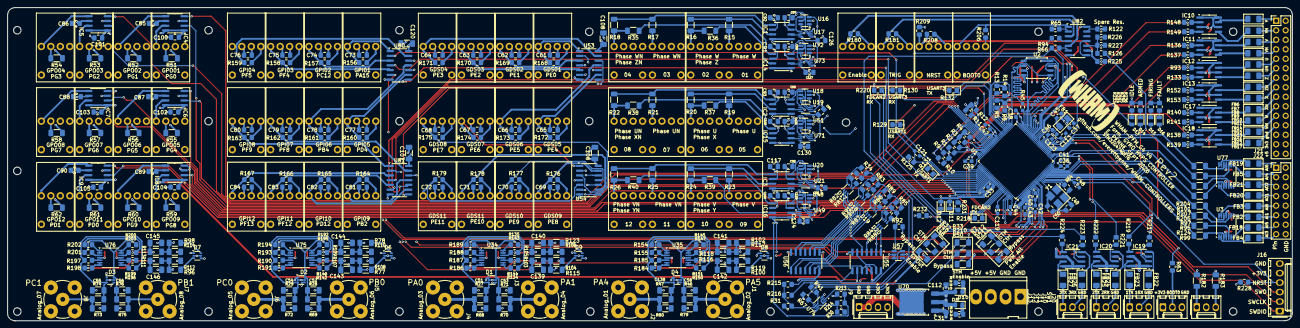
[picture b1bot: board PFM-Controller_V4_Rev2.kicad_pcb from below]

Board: 6 copper layers, 343.6 x 83.8 mm, 537 parts (441 on the bottom side), 410 nets.

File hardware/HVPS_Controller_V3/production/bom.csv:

Designator,Footprint,Quantity,Value,LCSC Part #
"C100, C101, C102, C103, C104, C105, C106, C107, C108, C112, C115, C116, C117, C118, C119, C120, C31, C33, C36, C37, C38, C39, C40, C41, C42, C43, C48, C61, C62, C63, C64, C65, C66, C67, C68, C69, C70, C71, C72, C73, C74, C75, C76, C77, C78, C79, C80, C81, C82, C83, C84, C85, C86, C87, C88, C89, C90, C91, C92, C93, C94, C95, C96, C97, C98, C99",0805,66,100n,
"C109, C110, C111, C114, C121, C122, C17, C18, C19, C20, C21, C22, C23, C24, C25, C26, C27, C28, C34, C35, C59, C60",1206,22,100n,
C44,0805,1,10u,
"C45, C47",0805,2,1u,
C46,0805,1,10n,
"D1, D2, D3, D4",SOT-363_SC-70-6,4,BAV99S,
"D17, D18, D19, D20",SOT-363_SC-70-6,4,CMKD4448,
"IC1, IC10, IC11, IC12, IC13, IC14, IC15, IC16, IC17, IC18, IC2, IC3, IC4, IC5, IC6, IC7, IC8, IC9",SOIC-8_5.3x5.3mm_P1.27mm,18,IX4340NTR,
J14,PinHeader_1x03_P2.54mm_Vertical,1,Jumper,
J9,Molex_KK-396_5273-02A_1x02_P3.96mm_Vertical,1,Molex 01x02,
"R1, R124, R2, R3, R30, R31, R32, R33, R4, R5, R6, R63, R65, R7, R8, R92, R94",0805,17,5K,
"R100, R101, R102, R133, R134, R135, R136, R137, R138, R139, R140, R141, R142, R143, R144, R145, R146, R147, R148, R149, R15, R150, R151, R152, R153, R154, R155, R16, R17, R18, R19, R20, R21, R22, R23, R24, R25, R26, R51, R52, R53, R54, R55, R56, R57, R58, R59, R60, R61, R62, R68, R69, R70, R72, R73, R75, R77, R79, R93, R95, R96, R97, R98, R99",1206,64,62,
"R103, R105, R107, R109, R111, R113, R115, R117",1206,8,2.5K,
"R104, R106, R108, R110, R112, R114, R116, R118, R27, R28, R29, R71, R74, R76, R78, R80",1206,16,5K,
"R119, R120, R121, R122, R125, R126, R127, R128, R129, R130, R131, R132, R34, R66, R81, R82, R83, R84, R85, R86, R87, R88, R89, R90, R91",0805,25,62,
R123,0805,1,2.5K,
U1,LQFP-128_14x14mm_P0.4mm,1,STM32G474QET6,
"U10, U11, U12, U13, U14, U15, U4, U5, U6, U7, U8, U9",Versalink-Vertical,12,VersalinkTX,
"U16, U18, U20, U57",SOT-23-6,4,SN74LVC2G14DBVR,
"U17, U19, U21, U74",SOP50P310X90-8N,4,SN74LVC2G08DCUT,
"U22, U23, U24, U25, U26, U27, U28, U29, U30, U31, U32, U33, U36, U37, U38, U39, U40, U41, U42, U43, U44, U45, U46, U47, U50, U52, U78",Versalink-Vertical,27,VersalinkRX,
"U3, U34, U35",TSSOP-14_4.4x5mm_P0.65mm,3,MCP6009,
"U53, U54, U80, U81, U82",SOIC-14_3.9x8.7mm_P1.27mm,5,74HC14,
"U55, U56",SOIC-14_3.9x8.7mm_P1.27mm,2,SN74HC21DR1G4,
U58,Versalink-Vertical,1,GPOut_01,
U59,Versalink-Vertical,1,GPOut_02,
U60,Versalink-Vertical,1,GPOut_03,
U61,Versalink-Vertical,1,GPOut_04,
U62,Versalink-Vertical,1,GPOut_05,
U63,Versalink-Vertical,1,GPOut_06,
U64,Versalink-Vertical,1,GPOut_07,
U65,Versalink-Vertical,1,GPOut_08,
U66,Versalink-Vertical,1,GPOut_09,
U67,Versalink-Vertical,1,GPOut_10,
U68,Versalink-Vertical,1,GPOut_11,
U69,Versalink-Vertical,1,GPOut_12,
U70,TO-252-3_TabPin2,1,AMS1117CD-3.3,
